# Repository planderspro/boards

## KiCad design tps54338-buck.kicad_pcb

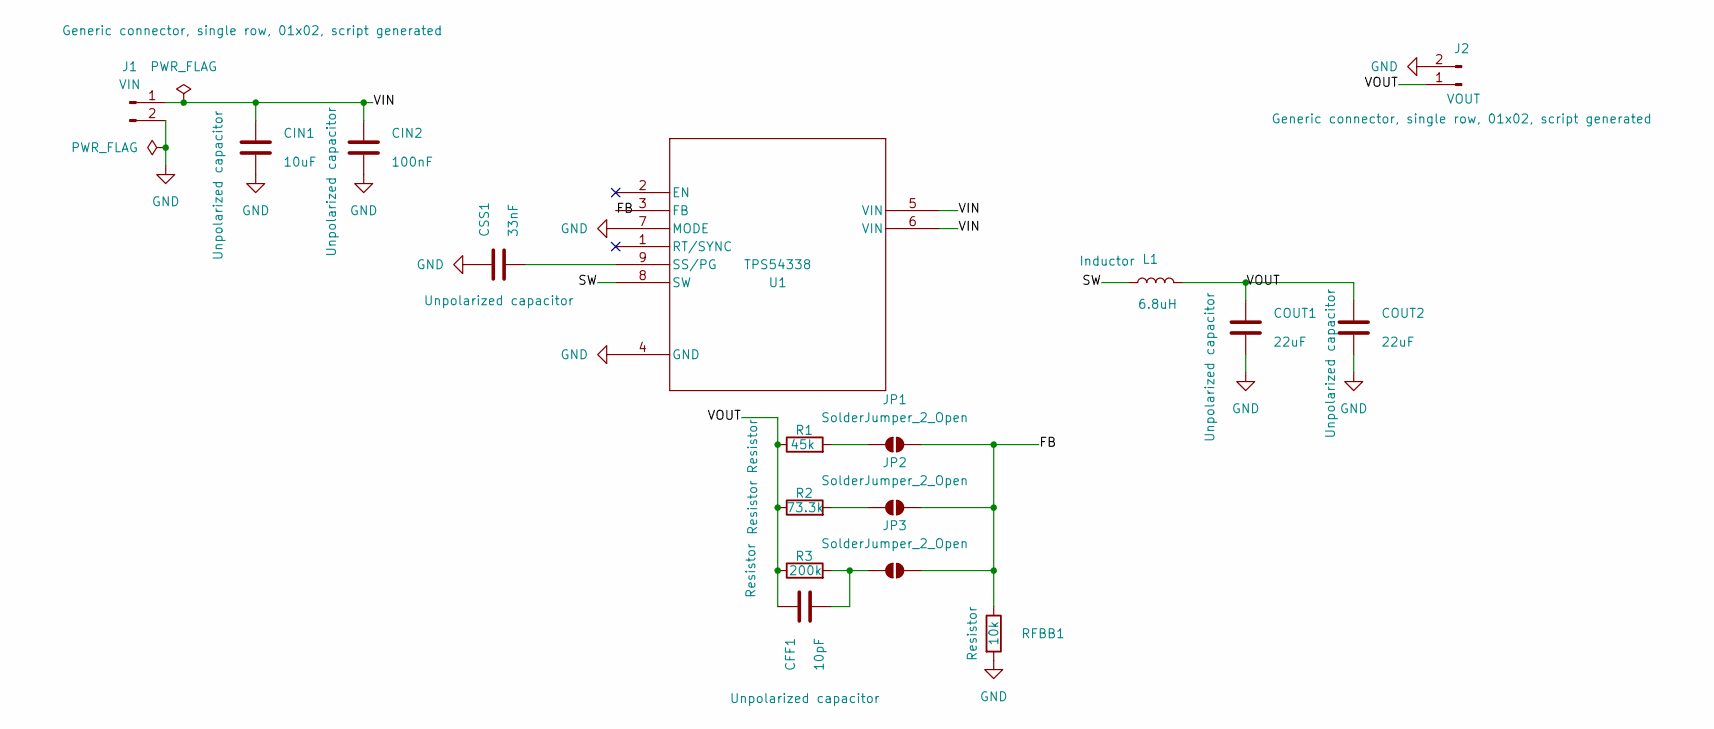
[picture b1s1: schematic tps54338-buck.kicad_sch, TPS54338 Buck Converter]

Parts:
CFF1: 10pF; C_0402_1005Metric
CIN1: 10uF; C_1210_3225Metric
CIN2: 100nF; C_0603_1608Metric
COUT1, COUT2: 22uF; C_1206_3216Metric
CSS1: 33nF; C_0603_1608Metric
J1: VIN; PinHeader_1x02_P2.54mm_Vertical
J2: VOUT; PinHeader_1x02_P2.54mm_Vertical
JP1, JP2, JP3: SolderJumper_2_Open; SolderJumper-2_P1.3mm_Open_Pad1.0x1.5mm
L1: 6.8uH; L_Bourns_SRN6045TA
R1: 45k; R_0402_1005Metric
R2: 73.3k; R_0402_1005Metric
R3: 200k; R_0402_1005Metric
RFBB1: 10k; R_0402_1005Metric
U1: TPS54338; TPS54338RQFR_VQFN_TXI_TEX

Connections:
/FB: JP1.2 (B), JP2.2 (B), JP3.2 (B), RFBB1.1, U1.3 (FB)
/SW: L1.1, U1.8 (SW)
/VIN: CIN1.1, CIN2.1, J1.1, U1.5 (VIN), U1.6 (VIN)
/VOUT: CFF1.1, COUT1.1, COUT2.1, J2.1, L1.2, R1.1, R2.1, R3.1
GND: CIN1.2, CIN2.2, COUT1.2, COUT2.2, CSS1.1, J1.2, J2.2, RFBB1.2, U1.4 (GND), U1.7 (MODE)
unnamed: JP1.1 (A), R1.2
unnamed: JP2.1 (A), R2.2
unnamed: CFF1.2, JP3.1 (A), R3.2
unnamed: CSS1.2, U1.9 (SS/PG)

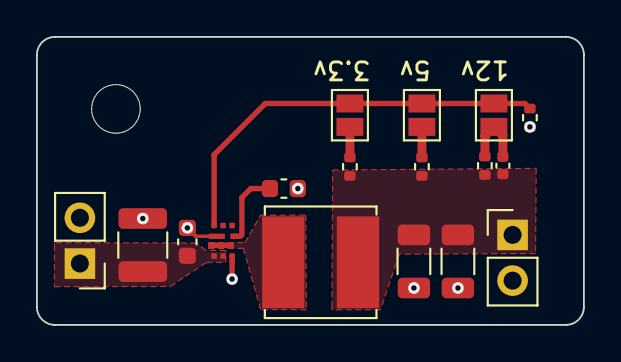
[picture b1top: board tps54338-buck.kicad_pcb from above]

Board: 2 copper layers, 30.4 x 16.0 mm, 17 parts (0 on the bottom side), 9 nets.

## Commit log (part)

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2026-04-08 Initial commit: TPS54338 buck converter project
